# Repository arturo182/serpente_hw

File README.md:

# Serpente

A tiny and cheap CircuitPython development board, perfect for quick projects and prototyping!

Comes in three versions: Female USB Type-C, Male USB Type-C, and bare PCB USB A plug.

# Technical details

- ATSAMD21E18A 32-bit Cortex-M0+ running at 48MHz
- 256KB flash and 32KB RAM
- 4MB Flash for storing files and CircuitPython code
- 6 highly customizable GPIOs
- 250mA LDO
- 3.3V logic and power
- Powered either from USB or external source
- User-controlled RGB LED
- Breadboardable headers
- Castellated edges, can be used as a module
- Mounting holes on the Female Type-C board

# Documentation

For more information visit https://serpente.solder.party/

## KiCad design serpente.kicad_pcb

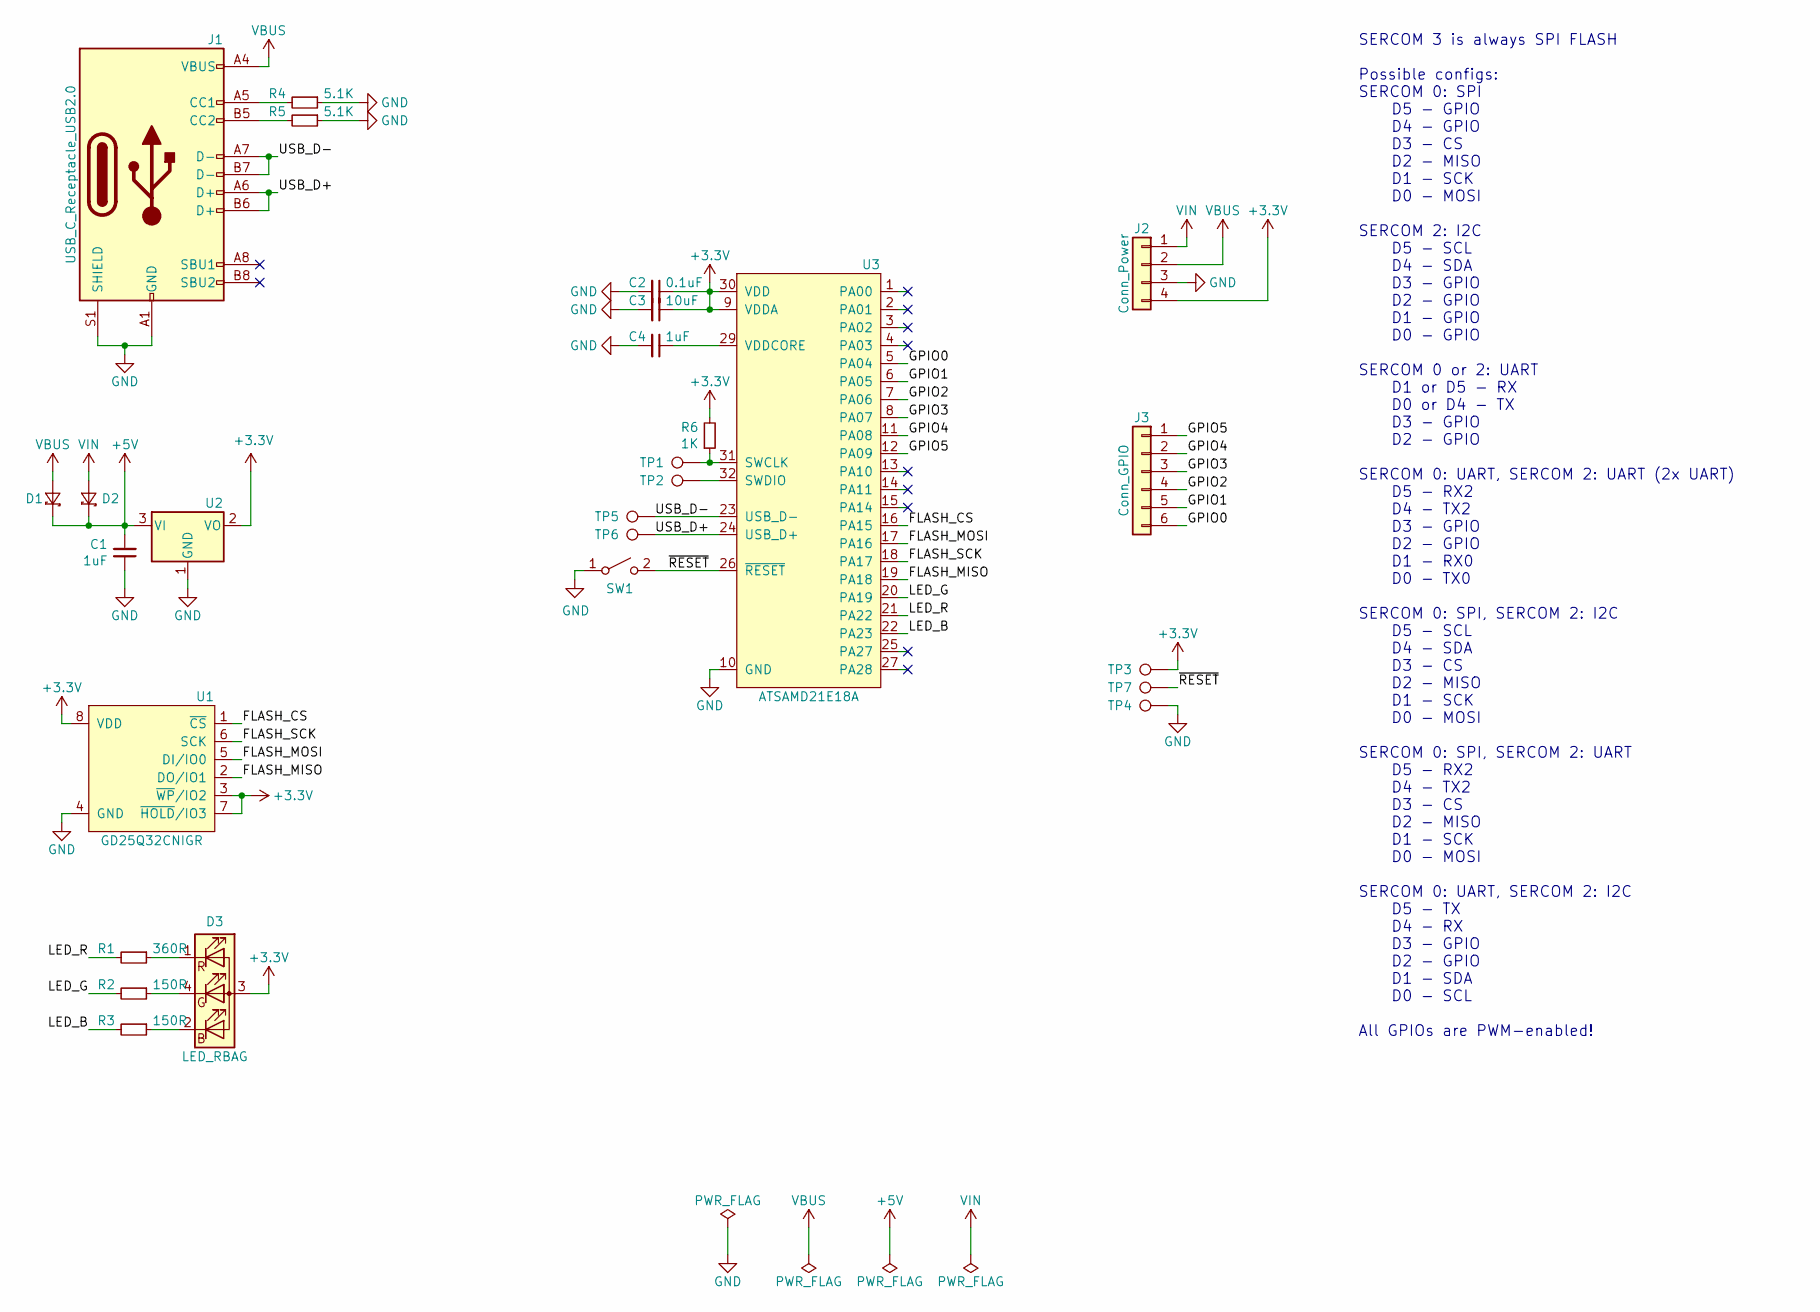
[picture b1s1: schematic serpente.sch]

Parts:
C1, C4: 1uF; C_0603_1608Metric
C2: 0.1uF; C_0603_1608Metric
C3: 10uF; C_0603_1608Metric
D1, D2: D_Schottky_Small; D_SOD-323_HandSoldering; LCSC C114023
D3: LED_RBAG; LED_Cree-PLCC4_2x2mm_CW; LCSC C108793
J1: USB_C_Receptacle_USB2.0; USB_C_Receptacle_GT-USB-7010; LCSC C319148
J2: Conn_Power; PinHeader_1x04_P2.54mm_Vertical_Castellated
J3: Conn_GPIO; PinHeader_1x06_P2.54mm_Vertical_Castellated
R1: 360R; R_0603_1608Metric
R2, R3: 150R; R_0603_1608Metric
R4, R5: 5.1K; R_0603_1608Metric
R6: 1K; R_0603_1608Metric
SW1: SW_RESET; SW_SPST_B3U-1000P-B; LCSC C128937
TP1: TP_SWCLK; TestPoint_Pad_D1.0mm
TP2: TP_SWDIO; TestPoint_Pad_D1.0mm
TP3: TP_VDD; TestPoint_Pad_D1.0mm
TP4: TP_GND; TestPoint_Pad_D1.0mm
TP5: TP_USB_D-; TestPoint_Pad_D1.0mm
TP6: TP_USB_D+; TestPoint_Pad_D1.0mm
TP7: TP_RESET; TestPoint_Pad_D1.0mm
U1: GD25Q32CNIGR; USON-8_3x4mm_P0.8mm
U2: MCP1700-3302E_SOT23; SOT-23; LCSC C83932
U3: ATSAMD21E18A; QFN-32-1EP_5x5mm_P0.5mm_EP3.6x3.6mm

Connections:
+3V3: C2.1, C3.1, D3.3 (A), J2.4, R6.2, TP3.1, U1.3 (~WP~/IO2), U1.7 (~HOLD~/IO3), U1.8 (VDD), U2.2 (VO), U3.9 (VDDA), U3.30 (VDD)
+5V: C1.2, D1.1 (K), D2.1 (K), U2.3 (VI)
/FLASH_CS: U1.1 (~CS~), U3.16 (PA15)
/FLASH_MISO: U1.2 (DO/IO1), U3.19 (PA18)
/FLASH_MOSI: U1.5 (DI/IO0), U3.17 (PA16)
/FLASH_SCK: U1.6 (SCK), U3.18 (PA17)
/GPIO0: J3.6, U3.5 (PA04)
/GPIO1: J3.5, U3.6 (PA05)
/GPIO2: J3.4, U3.7 (PA06)
/GPIO3: J3.3, U3.8 (PA07)
/GPIO4: J3.2, U3.11 (PA08)
/GPIO5: J3.1, U3.12 (PA09)
/LED_B: R3.2, U3.22 (PA23)
/LED_G: R2.2, U3.20 (PA19)
/LED_R: R1.2, U3.21 (PA22)
/USB_D+: J1.A6 (D+), J1.B6 (D+), TP6.1, U3.24 (USB_D+)
/USB_D-: J1.A7 (D-), J1.B7 (D-), TP5.1, U3.23 (USB_D-)
/~RESET~: SW1.2 (B), TP7.1, U3.26 (~RESET~)
GND: C1.1, C2.2, C3.2, C4.2, J1.A1 (GND), J1.A12 (GND), J1.B1 (GND), J1.B12 (GND), J1.S1 (SHIELD), J2.3, R4.1, R5.1, SW1.1 (A), TP4.1, U1.4 (GND), U2.1 (GND), U3.10 (GND), U3.28 (GND)
unnamed: C4.1, U3.29 (VDDCORE)
unnamed: D3.1 (RK), R1.1
unnamed: D3.2 (BK), R3.1
unnamed: D3.4 (GK), R2.1
unnamed: J1.A5 (CC1), R4.2
unnamed: J1.B5 (CC2), R5.2
unnamed: R6.1, TP1.1, U3.31 (SWCLK)
unnamed: TP2.1, U3.32 (SWDIO)
VBUS: D1.2 (A), J1.A4 (VBUS), J1.A9 (VBUS), J1.B4 (VBUS), J1.B9 (VBUS), J2.2
VIN: D2.2 (A), J2.1

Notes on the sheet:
SERCOM 3 is always SPI FLASH Possible configs: SERCOM 0: SPI D5 - GPIO D4 - GPIO D3 - CS D2 - MISO D1 - SCK D0 - MOSI SERCOM 2: I2C D5 - SCL D4 - SDA D3 - GPIO D2 - GPIO D1 - GPIO D0 - GPIO SERCOM 0 or 2: UART D1 or D5 - RX D0 or D4 - TX D3 - GPIO D2 - GPIO SERCOM 0: UART, SERCOM 2: UART (2x UART) 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

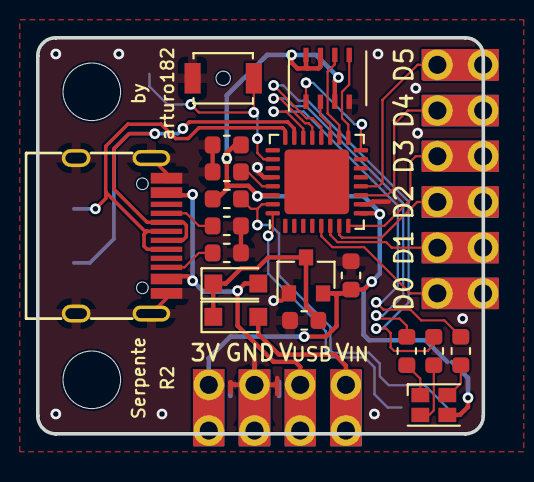
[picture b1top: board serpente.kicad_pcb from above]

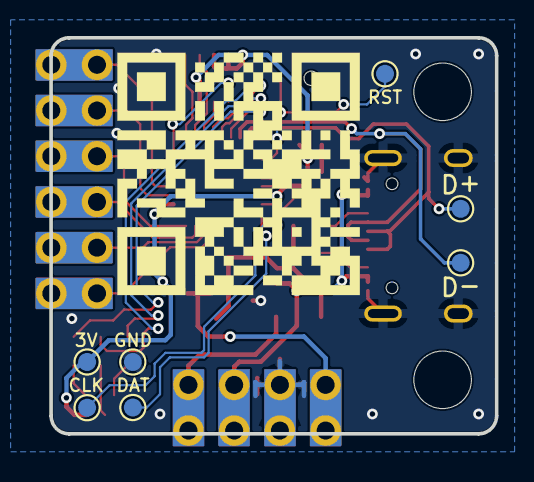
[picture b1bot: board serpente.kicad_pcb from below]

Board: 2 copper layers, 24.8 x 22.0 mm, 27 parts (7 on the bottom side), 29 nets.

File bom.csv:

Reference, Quantity, Value, Footprint, Datasheet, LCSC
C2 ,1,"0.1uF","Capacitor_SMD:C_0603_1608Metric","~"
C3 ,1,"10uF","Capacitor_SMD:C_0603_1608Metric","~"
C4 C1 ,2,"1uF","Capacitor_SMD:C_0603_1608Metric","~"
D1 D2 ,2,"D_Schottky_Small","Diode_SMD:D_SOD-323_HandSoldering","~","C114023"
D3 ,1,"LED_RBAG","LED_SMD:LED_Cree-PLCC4_2x2mm_CW","~","C108793"
J1 ,1,"USB_C_Receptacle_USB2.0","Connector_USB_Extra:USB_C_Receptacle_GT-USB-7010","https://www.usb.org/sites/default/files/documents/usb_type-c.zip","C319148"
J2 ,1,"Conn_Power","Connector_PinHeader_2.54mm_Extra:PinHeader_1x04_P2.54mm_Vertical_Castellated","~"
J3 ,1,"Conn_GPIO","Connector_PinHeader_2.54mm_Extra:PinHeader_1x06_P2.54mm_Vertical_Castellated","~"
R1 ,1,"360R","Resistor_SMD:R_0603_1608Metric","~"
R2 R3 ,2,"150R","Resistor_SMD:R_0603_1608Metric","~"
R4 R5 ,2,"5.1K","Resistor_SMD:R_0603_1608Metric","~"
R6 ,1,"1K","Resistor_SMD:R_0603_1608Metric","~"
SW1 ,1,"SW_RESET","Button_Switch_SMD:SW_SPST_B3U-1000P-B","~","C128937"
TP1 ,1,"TP_SWCLK","TestPoint:TestPoint_Pad_D1.0mm","~"
TP2 ,1,"TP_SWDIO","TestPoint:TestPoint_Pad_D1.0mm","~"
TP3 ,1,"TP_VDD","TestPoint:TestPoint_Pad_D1.0mm","~"
TP4 ,1,"TP_GND","TestPoint:TestPoint_Pad_D1.0mm","~"
TP5 ,1,"TP_USB_D-","TestPoint:TestPoint_Pad_D1.0mm","~"
TP6 ,1,"TP_USB_D+","TestPoint:TestPoint_Pad_D1.0mm","~"
TP7 ,1,"TP_RESET","TestPoint:TestPoint_Pad_D1.0mm","~"
U1 ,1,"GD25Q32CNIGR","Package_SON_Extra:USON-8_3x4mm_P0.8mm",""
U2 ,1,"MCP1700-3302E_SOT23","Package_TO_SOT_SMD:SOT-23","http://ww1.microchip.com/downloads/en/DeviceDoc/20001826D.pdf","C83932"
U3 ,1,"ATSAMD21E18A","Package_DFN_QFN:QFN-32-1EP_5x5mm_P0.5mm_EP3.6x3.6mm",""

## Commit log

2019-08-17 Initial import, WIP
2019-08-17 Add readme and fix text error in schematic
2019-08-18 Rev 1
2019-08-18 Add Plug variant, make header positions same between variants
2019-09-04 Fix GPIO numbers, add BOM, update README
2019-12-15 Final rev 2 release!
2019-12-21 Add CERN License
